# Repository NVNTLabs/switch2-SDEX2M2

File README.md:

# NVNT's SDEX2M2 (MicroSD Express to M.2) Adapter Project

SDEX2M2 (Micro**SD** **Ex**press to **M2**) is an adapter for the Nintendo Switch 2 which converts the MicroSD Express slot to a NVME M.2 (M-Key) slot. Think MicroSD Express cards are difficult to find or expensive? Looking to expand your storage for cheaper? Just use the NVME M.2 SSD that you have, and/or can easily find! The project is open source hardware under the GPLv3 License.

This project also encompasses the sister-project of "MicroSD Express to SD Express" adapter, which is a pin-to-pin conversion kit allowing full size SD Express cards to be used on the Nintendo Switch 2.

---

## 📚 Table of Contents
- **Introduction**
  - [Goals](#goals)
  - [Status](#status)
  - [Warnings](#warnings)
- **Assets & Hardware Info**
  - [Bill of Materials (BOM)](#bill-of-materials-bom)
  - [PINOUT & LEGEND](#pinout--legend)
    - [MicroSD Express to M.2 NVMe Mapping](#microsd-express-to-m2-nvme-mapping)
    - [M.2 NVMe Pinout](#m2-nvme-pinout)
    - [MicroSD Express Pinout](#microsd-express-pinout)
- **PCB's / Boards**
  - [Wiring Schematic](#wiring-schematic)
  - [MicroSD Express Dummy Card](#microsd-express-dummy-card)
  - [MicroSD Express to FPC Flex Cable Connector](#microsd-express-to-fpc-flex-cable-connector)
  - [MicroSD Express Breakout Board](#microsd-express-breakout-board)
  - [NVMe M.2 SSD Breakout Board](#nvme-m2-ssd-breakout-board)
  - [MicroSD Express to SD Express Prototype Adapter](#microsd-express-to-sd-express-prototype-adapter)
  - [SDEX2M2 MicroSD Express to NVMe M.2 Prototype Pin-to-Pin Adapter WIP](#sdex2m2-microsd-express-to-nvme-m2-prototype-pin-to-pin-adapter)
  - [MicroSD Express Sniffer for Switch 2 Handshake (UPDATED!) - USE THIS FOR SIGNAL CAPTURING](#microsd-express-sniffer)
- [License](#license)

---

## How is this possible?

This is possible because the Nintendo Switch 2's MicroSD Express slot supports the SD Express 7.1 standard, which exposes a **true PCIe Gen3 x1 interface** and utilizes the **NVMe protocol** for communication.

This adapter simply maps PCIe x1 from the Switch 2’s MicroSD Express slot to a standard M.2 2230 NVMe SSD. After further research and review from users, an onboard mcu/fpga will be required for the handshake process with the Switch 2.

Currently, we've developed a sniffer board which will be used to facilitate this.

---

## Goals

- ✅ Create Pinout & Pin Definitions (UPDATED!)
- ✅ Create Footprints for MicroSD Express
- ✅ Create Schematic for PCB layout
- ✅ Create Dummy MicroSD Express Card V2
- ✅ Create M.2 Breakout for prototyping (Updated 2-layer PCB)
- ✅ Create MicroSD Express Breakout Board V0.1 (Updated 2-layer PCB)
- ✅ Create MicroSD Express to SD Express Adapter (Experimental, Updated 2-layer PCB)
- ✅ Create BOM for fabrication and sourcing (WIP)
- ✅ Create MicroSD Express to NVMe M.2 SSD Pin to Pin Adapter (Proof of concept)
- ✅ Create basic 3D printable enclosures/shells for the PCBs
- ✅ Create MicroSD Express Sniffer PCB for capturing Nintendo Switch 2 Handshake (for getting NVMe drives to be functional!)
- ✅ Update MicroSD Express Sniffer PCB with new components and better grounding
- 🔲 Create MicroSD Express to NVMe M.2 SSD Adapter with FPGA/MCU Proto (for handshake with Nintendo Switch 2) **(in progress)**
- ✅ Create MicroSD Express to Flex Cable Adapter
- 🔲 Create Flex Cable to NVMe Adapter **(in progress)**
- 🔲 Create MicroSD Express to NVMe M.2 SSD Dock **(in progress)**

---

## Status

Work in progress. Currently, a prototype with handshake capability with the Switch 2 and also designs for the final product design are being worked on.

An early proof of concept prototype of the SDEX2M2 MicroSD Express to NVMe M.2 SSD Adapter has been made, but it does lack Switch 2 compatibility. 

**For prototyping, a new MicroSD Express sniffer has been uploaded which is used for capturing the signal/handshake that the Nintendo Switch 2 uses for communicating with the MicroSD Express card. With this, we are one step closer to our goal!**

Additionally, production-ready 2-layer PCBs for the MicroSD Express breakout board, NVMe breakout board, and the MicroSD Express to FPC Connector (which may be used in the final design) have been uploaded.

The MicroSD Express to SD Express adapter production ready prototype board has been uploaded as well, for users with full-size SD Express cards.

Basic 3D printable shells have been added too, for convenience.

---

## Warnings

- Use at your own risk. We are **not liable** for any damage to your drive, Switch 2, or other devices.
- Only use **low-voltage, low-power M.2 2230 NVMe drives**.
- **Do not use this in legacy MicroSD slots** (e.g., original Nintendo Switch).
  
---

## Bill of Materials (BOM)

| Reference | Quantity | Description                             | Part Number        | Manufacturer   |
|-----------|----------|-----------------------------------------|--------------------|----------------|
| J2        | 1        | M.2 Socket (M-Key, 2230)                | 114020             | Amphenol       |
| FB1       | 1        | Ferrite Bead 220Ω@100MHz 0603           | BLM18PG221SN1D     | Murata/OEM     |
| PCB       | 1        | 4-Layer PCB        | N/A                | Fabricated         | *              |
|*          | 1        | 10kΩ – 100kΩ Pull Up Resistor (Optional) | N/A               | *              |

The optional resistor is for the PERST# lane, may help with state when idle. Not sure if needed until prototyping commences.

---

## PINOUT & LEGEND

### MicroSD Express to M.2 NVMe Mapping

| microSD Express Pin  | PCIe Function | M.2 M-Key Pin(s) | M.2 Function         |
| -------------------- | ------------- | ---------------- | -------------------- |
| 7 (Row 1)            | REFCLK+       | B10              | REFCLK+              |
| 8 (Row 1)            | REFCLK−       | B11              | REFCLK−              |
| 2 (Row 1)            | PERST#        | A11              | PERST#               |
| 1 (Row 1)            | CLKREQ#       | B8               | CLKREQ#              |
| 11 (Row 2)           | TX+           | B23              | PCIe TX+             |
| 12 (Row 2)           | TX−           | B24              | PCIe TX−             |
| 14 (Row 2)           | RX-           | A21              | PCIe RX+             |
| 15 (Row 2)           | RX+           | A22              | PCIe RX−             |
| 4 (Row 1)            | 3.3V VDD      | B2, B3, B4       | 3.3V Power           |
| 6, 10, 13, 16     | GND           | A1, A4, etc.     | Ground               |

---

### M.2 NVMe Pinout

| Pin     | Name     | Function                 |
|---------|----------|--------------------------|
| A11     | PERST#   | PCIe Reset               |
| A21     | RX+      | PCIe RX+ (to host)       |
| A22     | RX−      | PCIe RX− (to host)       |
| B10     | REFCLK+  | PCIe Reference Clock +   |
| B11     | REFCLK−  | PCIe Reference Clock −   |
| B23     | TX+      | PCIe TX+ (from host)     |
| B24     | TX−      | PCIe TX− (from host)     |
| B2–B4   | 3.3V     | Power Supply             |
| A1, A4  | GND      | Ground Pins              |

---

### MicroSD Express Pinout

In SD Mode &* PCIe Mode

| Pin | Row 1 Contact | SD Mode Function | PCIe Mode Function               |
| --- | ------------- | -------------------- | ---------------------------- |
| 1   | DAT2          | Data Line 2          | CLKREQ# (Power / Signal Mgmt)         |
| 2   | DAT3 / CD     | Data Line 3 / CD     | PERST# (Reset)               |
| 3   | CMD           | Command Line         | CMD (unused in PCIe mode)    |
| 4   | VDD           | 3.3V Power           | 3.3V Power                   |
| 5   | CLK           | Clock Line           | CLK (unused in PCIe mode)    |
| 6   | VSS           | Ground               | Ground                       |
| 7   | DAT0          | Data Line 0          | REFCLK+ (PCIe Ref Clock)     |
| 8   | DAT1          | Data Line 1          | REFCLK− (PCIe Ref Clock)     |

| Pin | Row 2 Contact   | PCIe Function                 |
| --- | --------------- | ----------------------------- |
| 9   | 1V8             | 1.8 Volts                     |
| 10  | VSS2            | Ground for isolation          |
| 11  | TX+             | PCIe TX+ (Transmit)           |
| 12  | TX-             | PCIe TX- (Transmit)           |
| 13  | VSS3            | Ground for isolation          |
| 14  | RX-             | PCIe RX- (Receive)            |
| 15  | RX+             | PCIe RX+ (Receive)            |
| 16  | VSS4            | Ground for isolation          |
| 17  | 1V2             | 1.2 Volts                     |

Please note: Row 2 is only operational in PCIe Mode. Row 2 is based on M1cha's (https://github.com/M1cha/sdexpress_pcbs) schematic.

---

### MicroSD Express Card to SD Express Slot Pinout

| **MicroSD Express Pin** | **Function (PCIe Mode)**  | **SD Express Slot Pin** | **Function in Slot** | 
| ----------------------- | ------------------------- | ----------------------- | -------------------- | 
| 1 DAT2                  | CLKREQ#                   | 51                      | CLKREQ# (Power / Signal Mgmt) | 
| 2 DAT3 / CD             | PERST#                    | 52                      | PERST# (Reset line)  |
| 3 CMD                   | CMD (unused)              | —                       | CMD (unused in PCIe mode) | 
| 4 VDD                   | 3.3V VDD                  | 18, 48                  | VDD                  |
| 5 CLK                   | CLK (unused)              | —                       | —                    | 
| 6 VSS                   | GND (VSS1)                | 17, 47, 49, 50          | GND                  |
| 7 DAT0                  | REFCLK+                   | 45                      | REFCLK+              | 
| 8 DAT1                  | REFCLK−                   | 46                      | REFCLK−              | 
| 9 1V8                   | 1.8V VDD (VDD2)           | 1, 2, 3 (often shared)  | VDD 1.8 Volts        | 
| 10 VSS2                 | GND (VSS2)                | 17, 47, etc.            | GND (GND Ground for isolation)| 
| 11 TX+                  | TX+                       | 39                      | PCIe TX+ (Transmit)  |
| 12 TX-                  | TX−                       | 41                      | PCIe TX- (Transmit)  |
| 13 VSS3                 | GND  (VSS3)               | 17, 47, etc.            | GND (Ground for isolation)| 
| 14 RX-                  | RX−                       | 35                      | PCIe RX- (Receive)|
| 15 RX+                  | RX+                       | 37                      | PCIe RX+ (Receive)|
| 16 VSS4                 | GND (VSS4)                | 17, 47, etc.            | GND (Ground for isolation)|                 
| 17 1V2                  | 1.2V VDD (VDD3, optional) | —                       | Not used (May be unused)|

Note: WIP

---

### Wiring Schematic

Still a WIP. Some discrepencies may exist.

---

### MicroSD Express Dummy Card

A dummy card has been created (thanks to M1cha's design examples!), for reference. Files have been attached.

---

### MicroSD Express to FPC Flex Cable Connector

A MicroSD Express to Flex Cable Connector (FPC) has been created for reference. Schematic, Geberer and PCB files have been attached.

---

### MicroSD Express Breakout Board

A production-ready 2-layer breakout board for MicroSD Express has been created (codenamed: "The Key"). Files have been attached in the repo. The purpose of this is for prototyping with a breadboard.

---

### NVMe M2 SSD Breakout Board

A breakout board for a NVMe M.2 SSD slot (M-key) has been created. Files have been attached in the repo. The purpose of this is for prototyping with a breadboard.

---

### MicroSD Express to SD Express Prototype Adapter

An extremely experimental production ready MicroSD Express to **Full Size** SD Express Slot adapter has been made. The purpose of this is to allow full size SD Express cards to be inserted into the Nintendo Switch 2.

Please be aware that it is untested as of the time of writing.

---

### SDEX2M2 MicroSD Express to NVMe M.2 Prototype Pin-to-Pin Adapter

A production-ready (but experimental) 2-layer PCB for the SDEX2M2 MicroSD Express to NVMe M.2 adapter has been uploaded. 

Please note that this is a pin-to-pin adapter, and is **not capable of completing the handshake with Nintendo Switch 2**. It is a proof of concept board.

---

### MicroSD Express Sniffer

**Newly updated!**

A experimental PCB MicroSD Express sniffer has been uploaded and updated. **This is used for capturing the handshake signal/commands from the Nintendo Switch 2**, which will be used to create the final SDEX2M2 Switch 2 NVME M.2 Drive Adapter.

Now updated to use an Amphenol MicroSD Express Slot and with updated grounding for better signal isolation.

---

## License

This hardware design is licensed under the **CERN Open Hardware License Version 2 – Strongly Reciprocal (CERN-OHL-S v2)**.

The software/firmware design is licensed under the **GNU General Public License v3.0 (GPLv3)**

The documentation and readme is licensed under the **Creative Commons Attribution-ShareAlike 4.0 International (CC-BY-SA 4.0)**.

See [LICENSE](LICENSE.txt), [LICENSE-HARDWARE](LICENSE-HARDWARE.txt) and [LICENSE-DOCUMENTATION](LICENSE-DOCUMENTATION.txt) for more information.

---

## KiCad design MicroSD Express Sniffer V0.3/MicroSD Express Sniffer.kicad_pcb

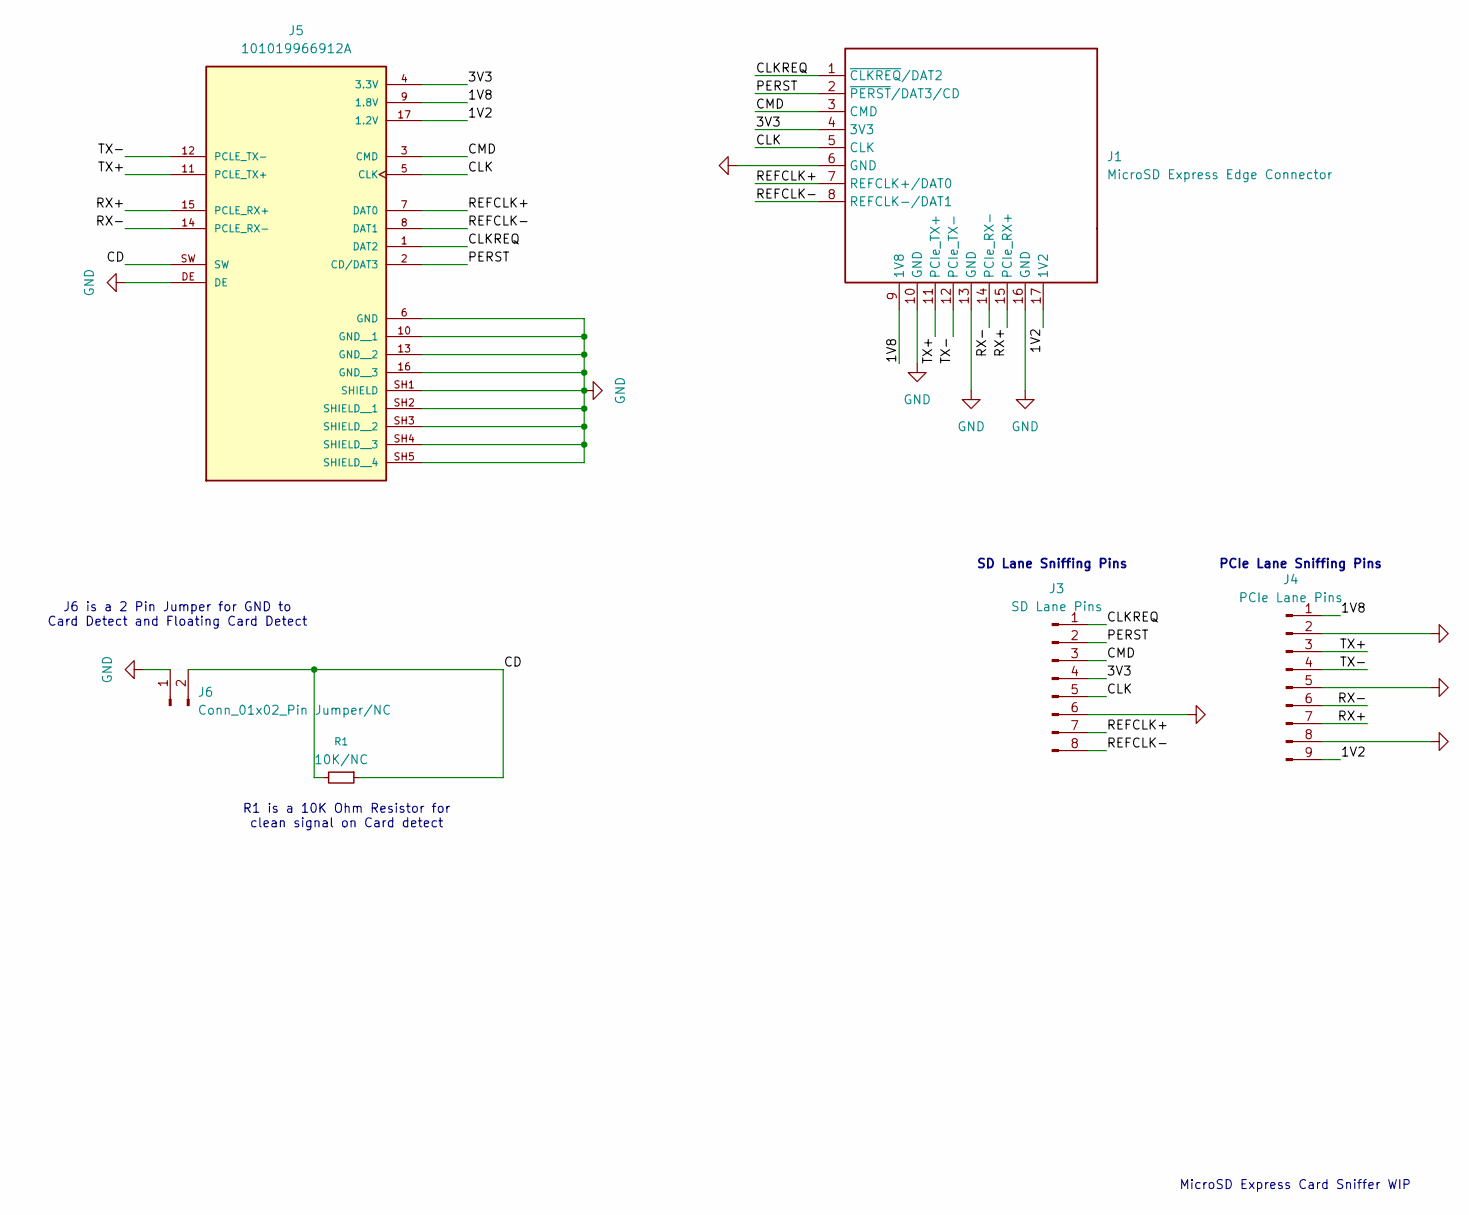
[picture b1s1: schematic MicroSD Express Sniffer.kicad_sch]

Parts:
J1: MicroSD Express Edge Connector; usdex-male-open_bottom
J3: SD Lane Pins; PinHeader_1x08_P2.54mm_Vertical
J4: PCIe Lane Pins; PinHeader_1x09_P2.54mm_Vertical
J5: 101019966912A; AMPHENOL_101019966912A SDEX2M2; PARTREV 10
J6: Conn_01x02_Pin Jumper/NC; PinHeader_1x02_P2.54mm_Vertical
R1: 10K/NC; R_0603_1608Metric

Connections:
/1V2: J1.17 (1V2), J4.9, J5.17 (1.2V)
/1V8: J1.9 (1V8), J4.1, J5.9 (1.8V)
/3V3: J1.4 (3V3), J3.4, J5.4 (3.3V)
/CD: J5.SW, J6.2, R1.1, R1.2
/CLK: J1.5 (CLK), J3.5, J5.5 (CLK)
/CLKREQ: J1.1 (~CLKREQ/DAT2), J3.1, J5.1 (DAT2)
/CMD: J1.3 (CMD), J3.3, J5.3 (CMD)
/PERST: J1.2 (~PERST/DAT3/CD), J3.2, J5.2 (CD/DAT3)
/REFCLK+: J1.7 (REFCLK+/DAT0), J3.7, J5.7 (DAT0)
/REFCLK-: J1.8 (REFCLK-/DAT1), J3.8, J5.8 (DAT1)
/RX+: J1.15 (PCIe_RX+), J4.7, J5.15 (PCLE_RX+)
/RX-: J1.14 (PCIe_RX-), J4.6, J5.14 (PCLE_RX-)
/TX+: J1.11 (PCIe_TX+), J4.3, J5.11 (PCLE_TX+)
/TX-: J1.12 (PCIe_TX-), J4.4, J5.12 (PCLE_TX-)
GND: J1.6 (GND), J1.10 (GND), J1.13 (GND), J1.16 (GND), J3.6, J4.2, J4.5, J4.8, J5.6 (GND), J5.10 (GND__1), J5.13 (GND__2), J5.16 (GND__3), J5.DE, J5.SH1 (SHIELD), J5.SH2 (SHIELD__1), J5.SH3 (SHIELD__2), J5.SH4 (SHIELD__3), J5.SH5 (SHIELD__4), J6.1

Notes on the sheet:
SD Lane Sniffing Pins
R1 is a 10K Ohm Resistor for clean signal on Card detect
J6 is a 2 Pin Jumper for GND to Card Detect and Floating Card Detect
PCIe Lane Sniffing Pins
MicroSD Express Card Sniffer WIP

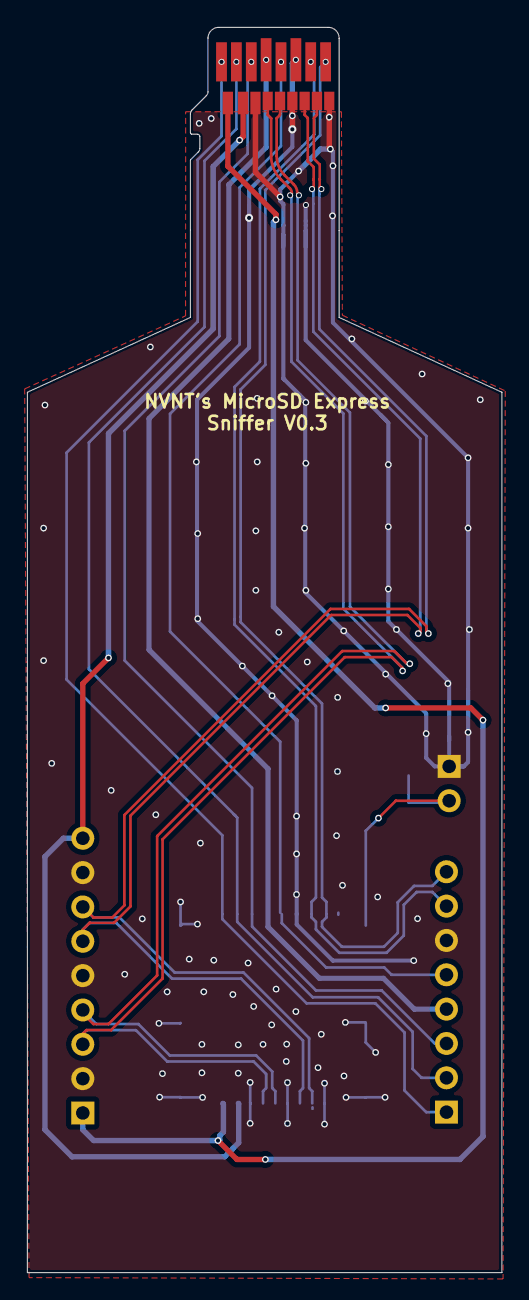
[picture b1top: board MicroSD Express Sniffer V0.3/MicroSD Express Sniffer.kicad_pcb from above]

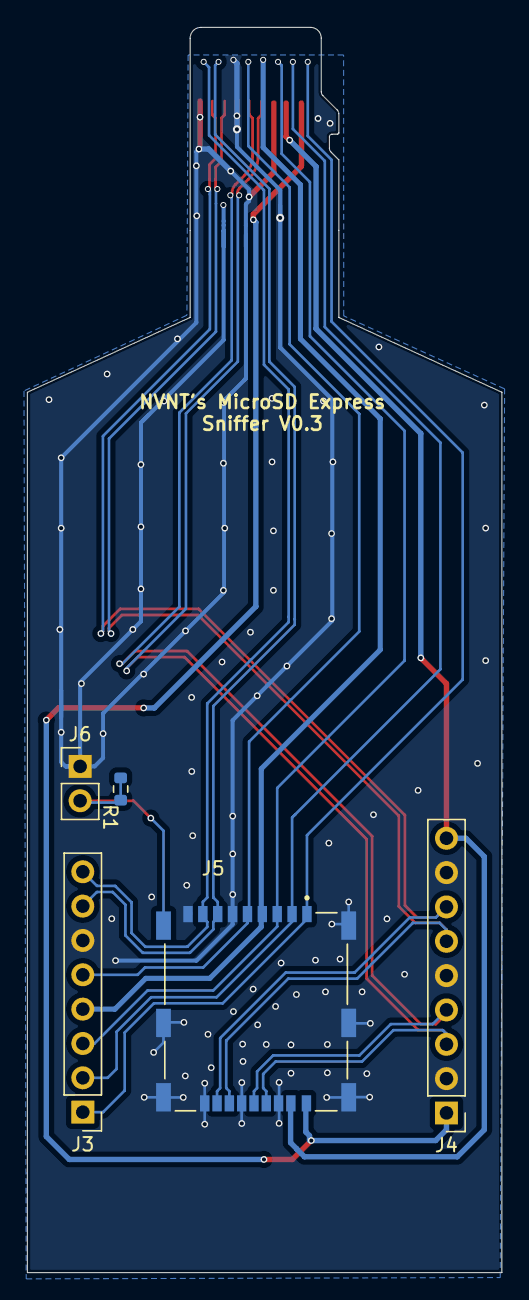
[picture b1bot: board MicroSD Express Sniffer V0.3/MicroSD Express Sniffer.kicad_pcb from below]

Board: 2 copper layers, 35.1 x 92.1 mm, 6 parts (5 on the bottom side), 15 nets.

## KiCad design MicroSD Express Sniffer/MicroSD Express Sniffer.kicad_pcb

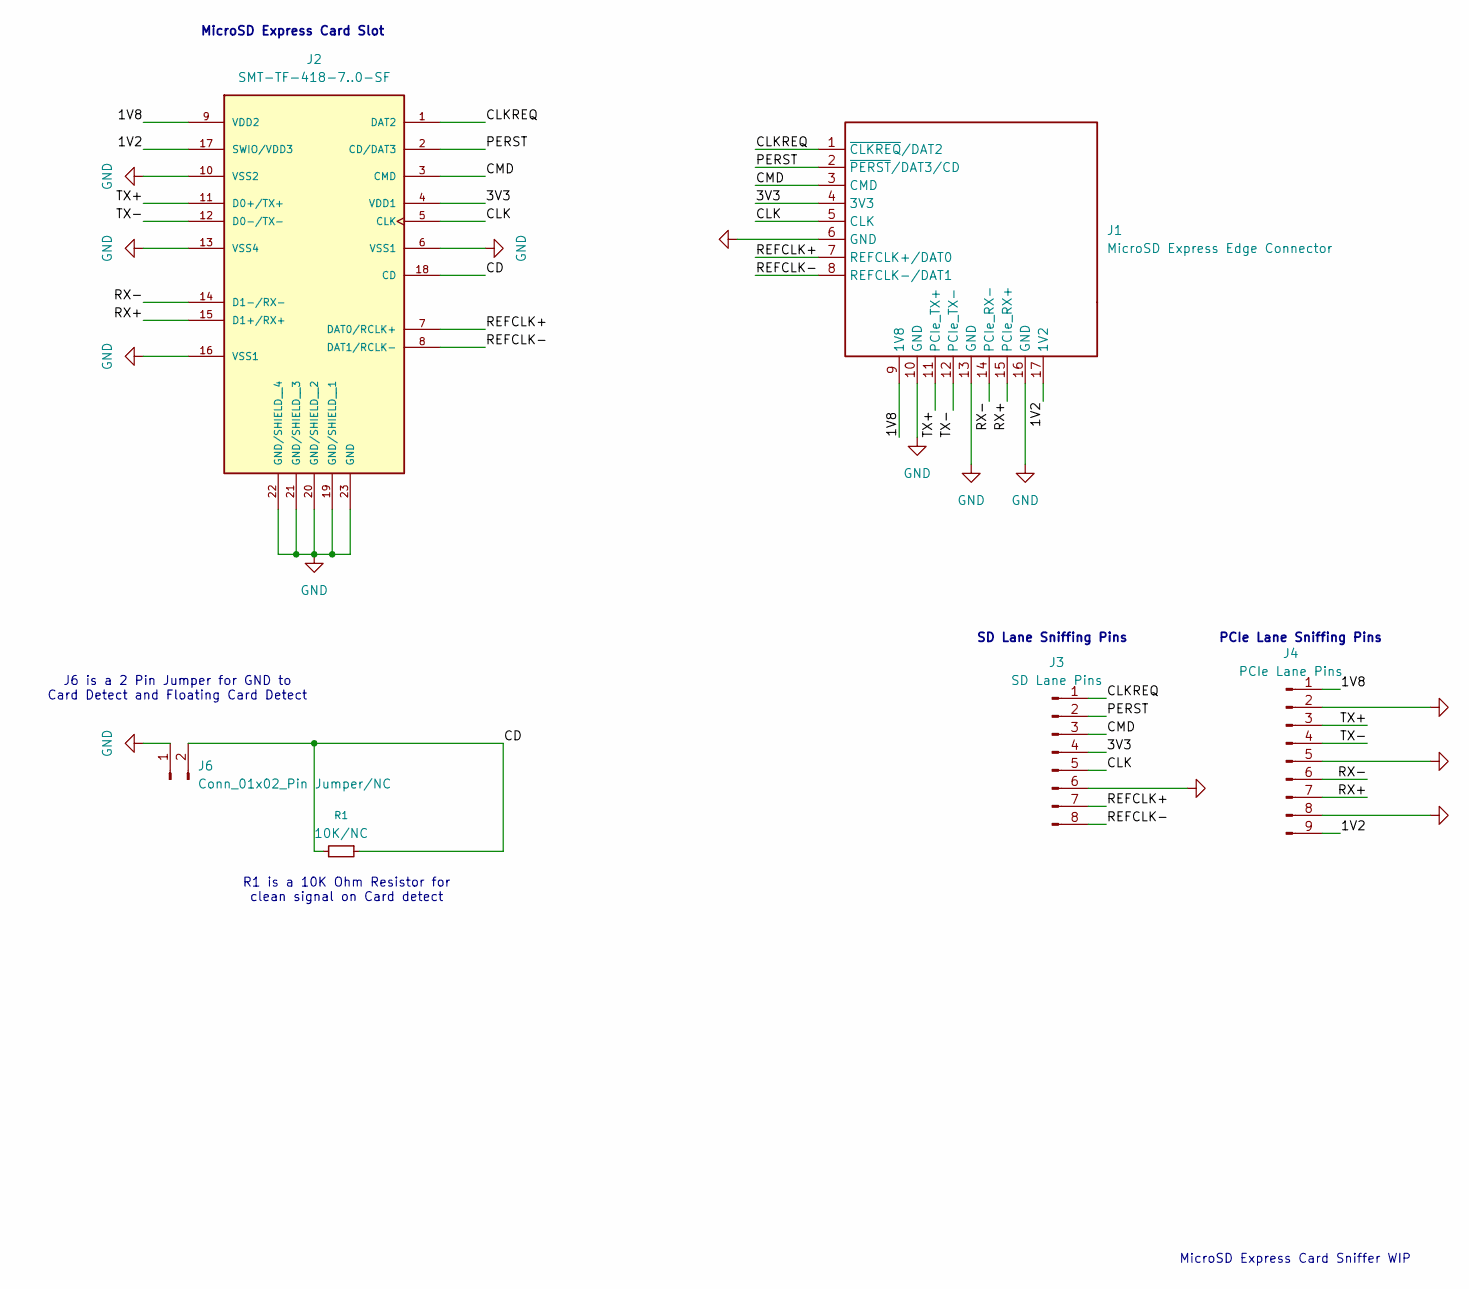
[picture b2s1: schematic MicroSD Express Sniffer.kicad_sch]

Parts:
J1: MicroSD Express Edge Connector; usdex-male-open_bottom
J2: SMT-TF-418-7..0-SF; SMT_TF_418__7.0_SF; PARTREV AX6
J3: SD Lane Pins; PinHeader_1x08_P2.54mm_Vertical
J4: PCIe Lane Pins; PinHeader_1x09_P2.54mm_Vertical
J6: Conn_01x02_Pin Jumper/NC; PinHeader_1x02_P2.54mm_Vertical
R1: 10K/NC; R_0603_1608Metric

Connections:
/1V2: J1.17 (1V2), J2.17 (SWIO/VDD3), J4.9
/1V8: J1.9 (1V8), J2.9 (VDD2), J4.1
/3V3: J1.4 (3V3), J2.4 (VDD1), J3.4
/CD: J2.18 (CD), J6.2, R1.1, R1.2
/CLK: J1.5 (CLK), J2.5 (CLK), J3.5
/CLKREQ: J1.1 (~CLKREQ/DAT2), J2.1 (DAT2), J3.1
/CMD: J1.3 (CMD), J2.3 (CMD), J3.3
/PERST: J1.2 (~PERST/DAT3/CD), J2.2 (CD/DAT3), J3.2
/REFCLK+: J1.7 (REFCLK+/DAT0), J2.7 (DAT0/RCLK+), J3.7
/REFCLK-: J1.8 (REFCLK-/DAT1), J2.8 (DAT1/RCLK-), J3.8
/RX+: J1.15 (PCIe_RX+), J2.15 (D1+/RX+), J4.7
/RX-: J1.14 (PCIe_RX-), J2.14 (D1-/RX-), J4.6
/TX+: J1.11 (PCIe_TX+), J2.11 (D0+/TX+), J4.3
/TX-: J1.12 (PCIe_TX-), J2.12 (D0-/TX-), J4.4
GND: J1.6 (GND), J1.10 (GND), J1.13 (GND), J1.16 (GND), J2.6 (VSS1), J2.10 (VSS2), J2.13 (VSS4), J2.16 (VSS1), J2.19 (GND/SHIELD__1), J2.20 (GND/SHIELD__2), J2.21 (GND/SHIELD__3), J2.22 (GND/SHIELD__4), J2.23 (GND), J3.6, J4.2, J4.5, J4.8, J6.1

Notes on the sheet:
SD Lane Sniffing Pins
R1 is a 10K Ohm Resistor for clean signal on Card detect
J6 is a 2 Pin Jumper for GND to Card Detect and Floating Card Detect
MicroSD Express Card Slot
PCIe Lane Sniffing Pins
MicroSD Express Card Sniffer WIP

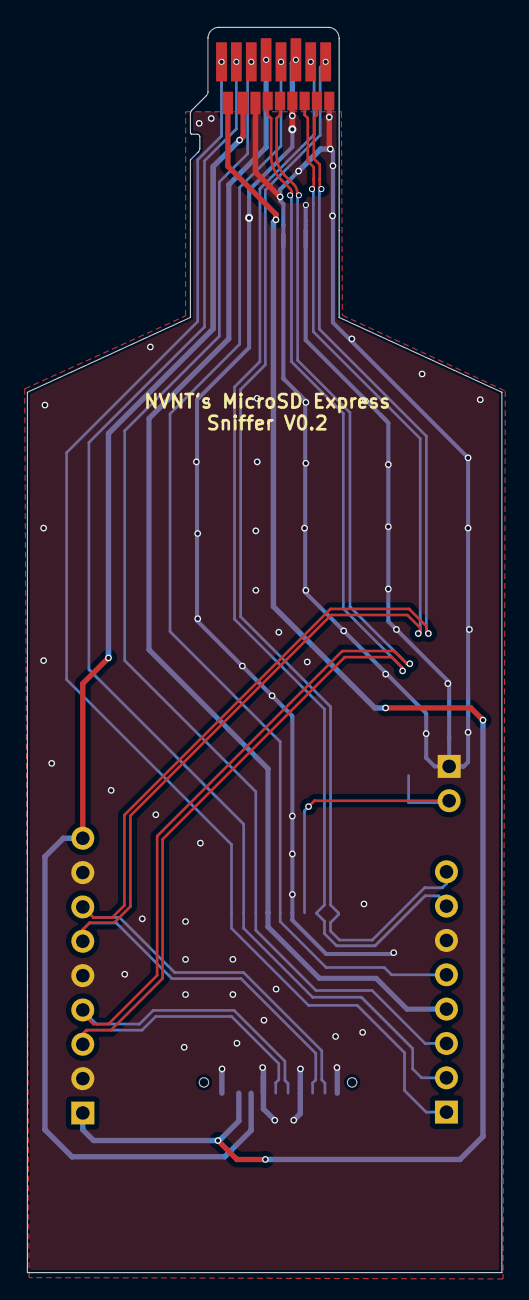
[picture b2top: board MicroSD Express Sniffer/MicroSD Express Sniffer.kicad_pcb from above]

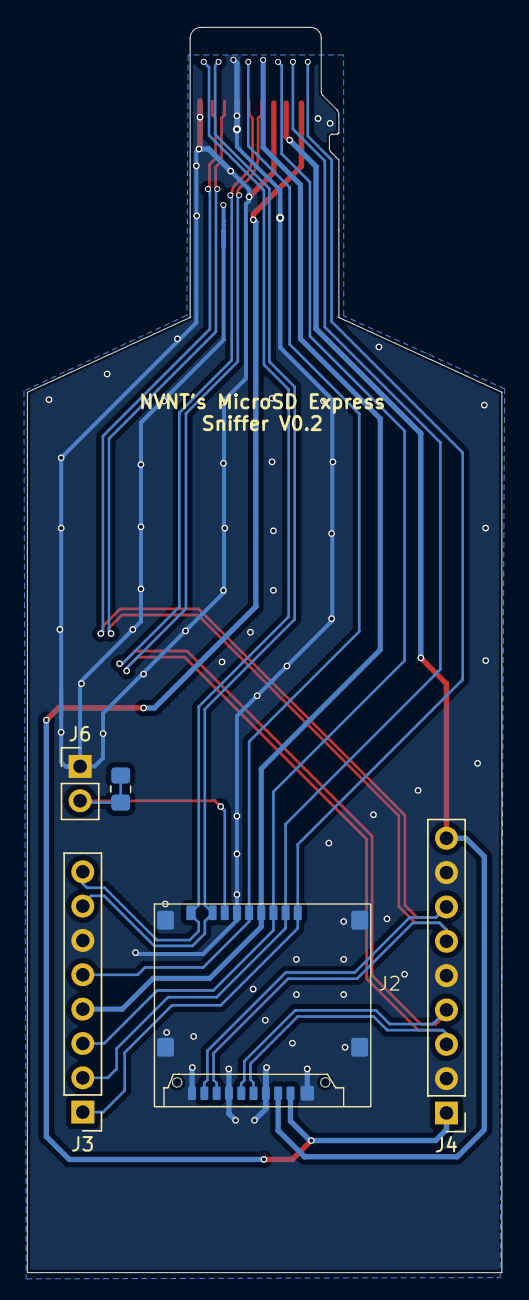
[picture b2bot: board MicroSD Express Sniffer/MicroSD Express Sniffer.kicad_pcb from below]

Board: 2 copper layers, 35.1 x 92.1 mm, 6 parts (5 on the bottom side), 15 nets.

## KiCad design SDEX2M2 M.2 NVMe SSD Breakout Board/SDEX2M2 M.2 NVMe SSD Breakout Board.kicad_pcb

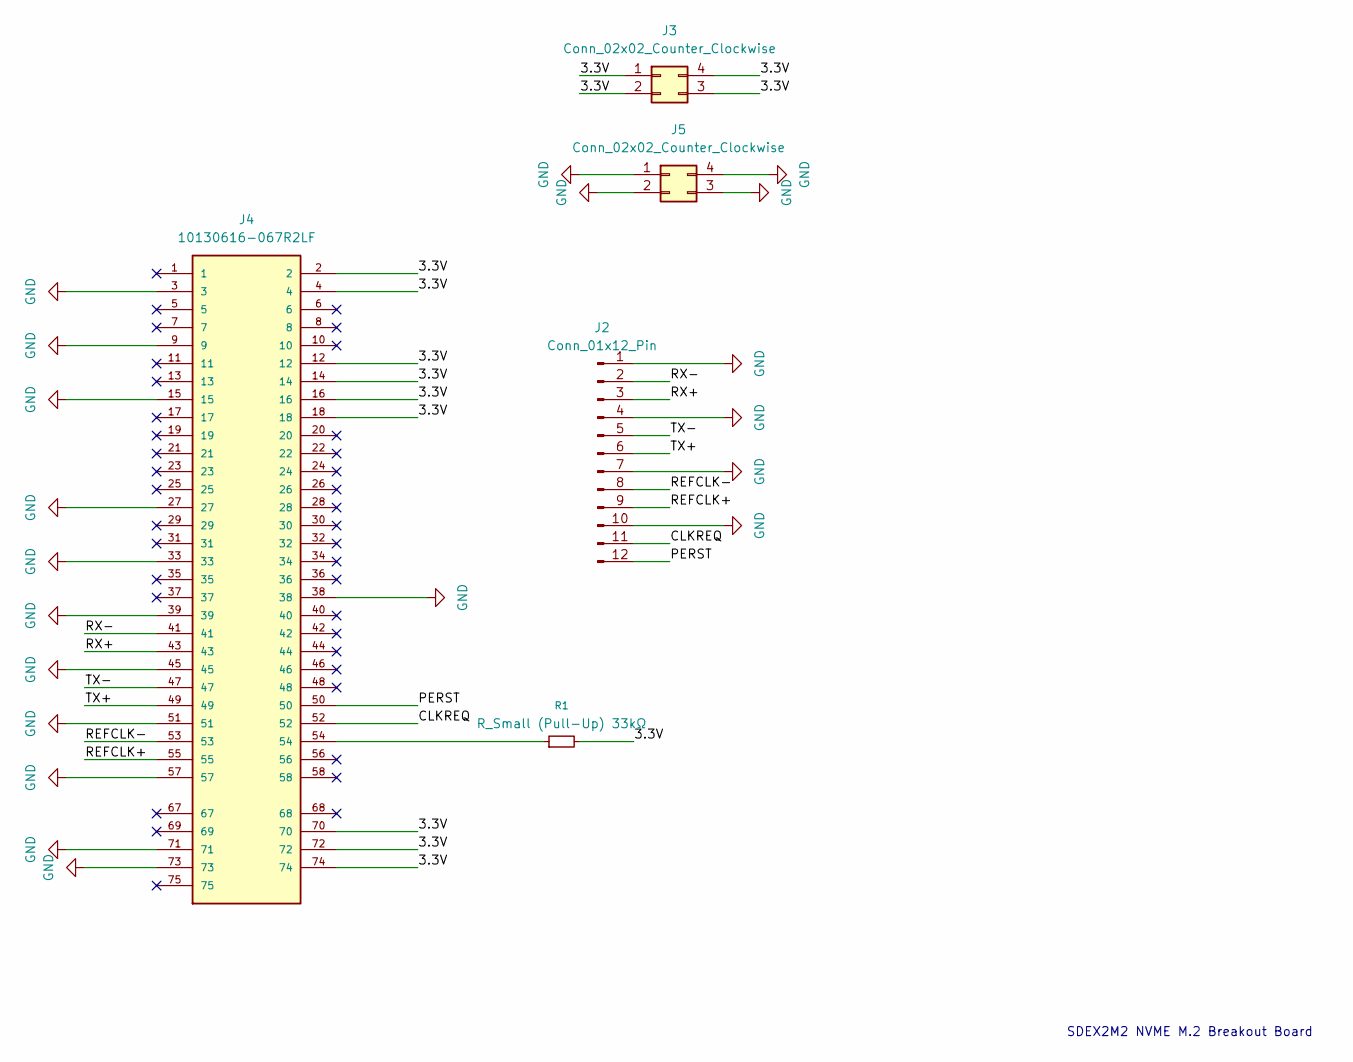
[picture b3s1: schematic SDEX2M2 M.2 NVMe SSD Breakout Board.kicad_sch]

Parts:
J2: Conn_01x12_Pin; PinHeader_1x12_P2.00mm_Vertical
J3, J5: Conn_02x02_Counter_Clockwise; PinHeader_2x02_P2.00mm_Vertical
J4: 10130616-067R2LF; AMPHENOL_10130616-067R2LF; PARTREV C
R1: R_Small (Pull-Up) 33kΩ; R_0603_1608Metric

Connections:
/3.3V: J3.1, J3.2, J3.3, J3.4, J4.2, J4.4, J4.12, J4.14, J4.16, J4.18, J4.70, J4.72, J4.74, R1.2
/CLKREQ: J2.11, J4.52
/PERST: J2.12, J4.50
/REFCLK+: J2.9, J4.55
/REFCLK-: J2.8, J4.53
/RX+: J2.3, J4.43
/RX-: J2.2, J4.41
/TX+: J2.6, J4.49
/TX-: J2.5, J4.47
GND: J2.1, J2.4, J2.7, J2.10, J4.3, J4.9, J4.15, J4.27, J4.33, J4.38, J4.39, J4.45, J4.51, J4.57, J4.71, J4.73, J5.1, J5.2, J5.3, J5.4
unnamed: J4.54, R1.1

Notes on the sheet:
SDEX2M2 NVME M.2 Breakout Board

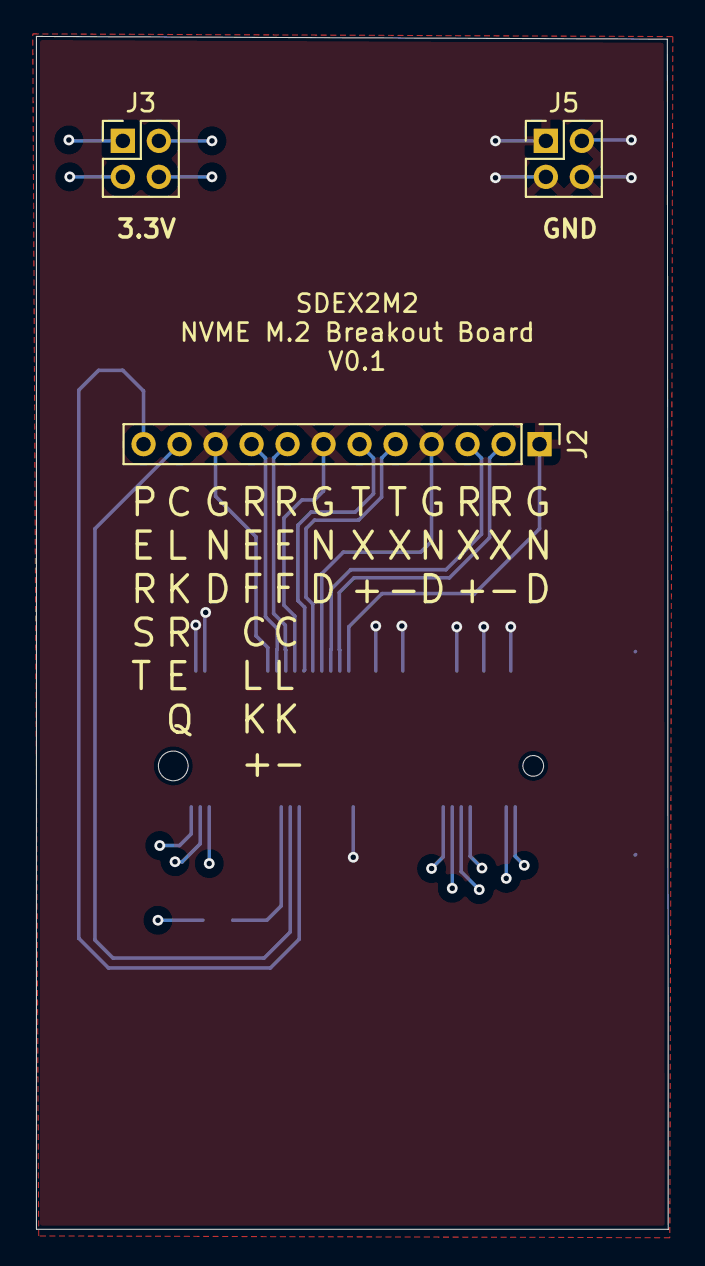
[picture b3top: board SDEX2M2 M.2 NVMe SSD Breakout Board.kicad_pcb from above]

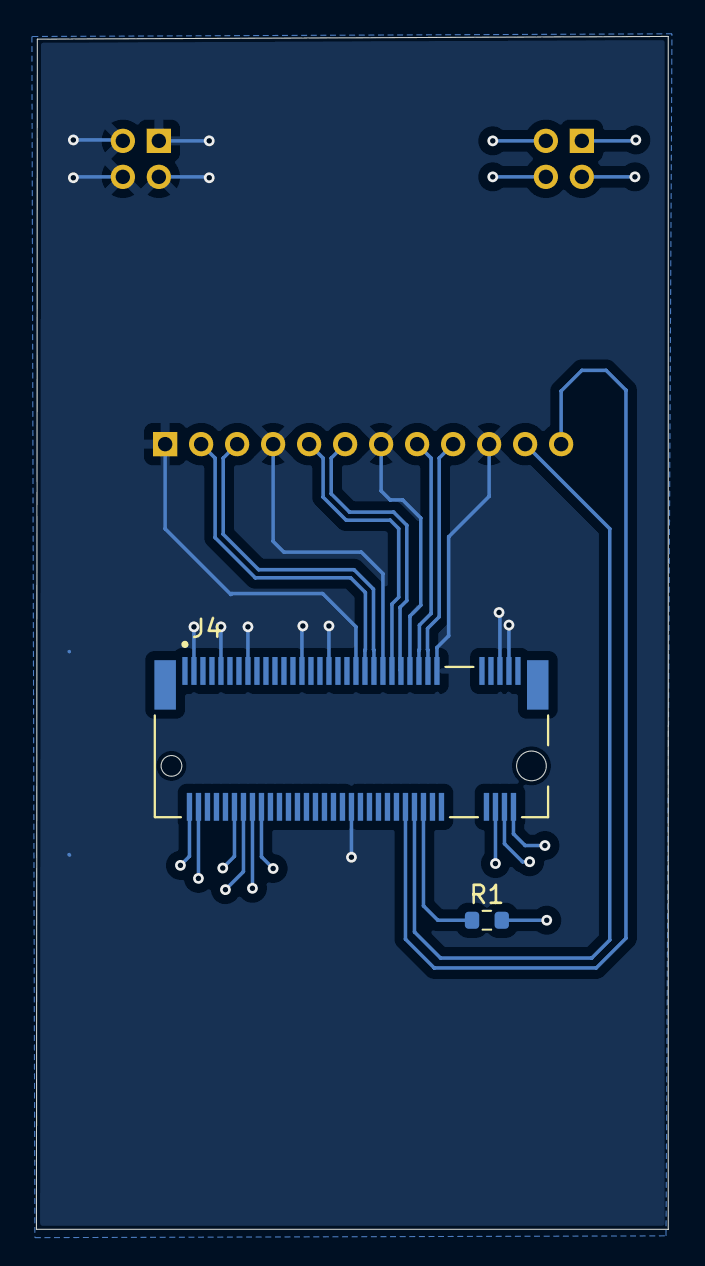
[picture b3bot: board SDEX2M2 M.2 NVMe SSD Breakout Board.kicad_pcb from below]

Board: 6 copper layers, 35.1 x 66.3 mm, 5 parts (2 on the bottom side), 11 nets.

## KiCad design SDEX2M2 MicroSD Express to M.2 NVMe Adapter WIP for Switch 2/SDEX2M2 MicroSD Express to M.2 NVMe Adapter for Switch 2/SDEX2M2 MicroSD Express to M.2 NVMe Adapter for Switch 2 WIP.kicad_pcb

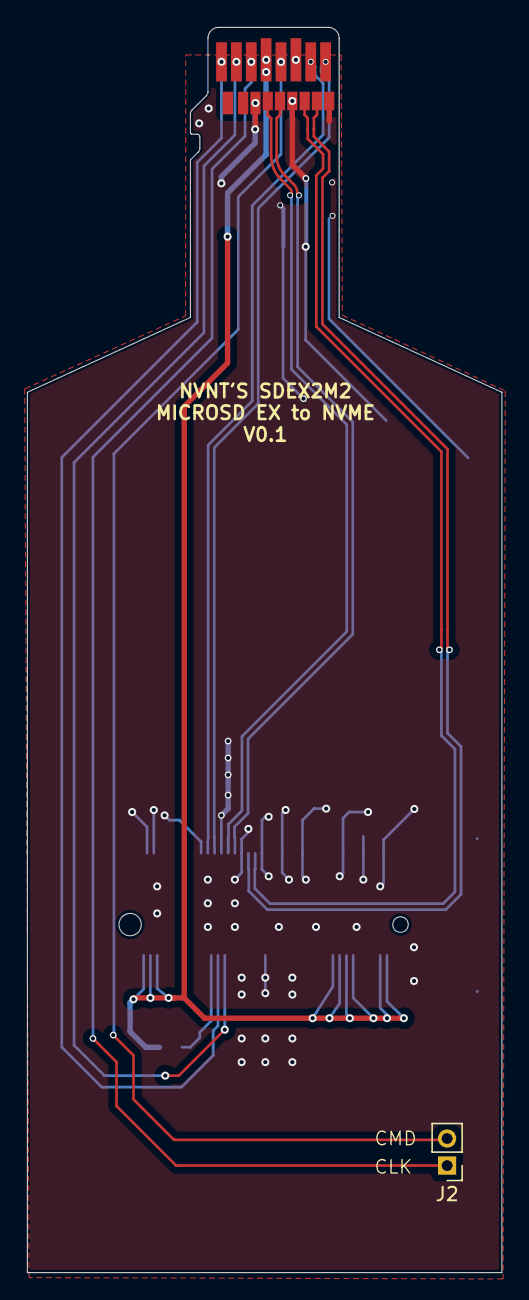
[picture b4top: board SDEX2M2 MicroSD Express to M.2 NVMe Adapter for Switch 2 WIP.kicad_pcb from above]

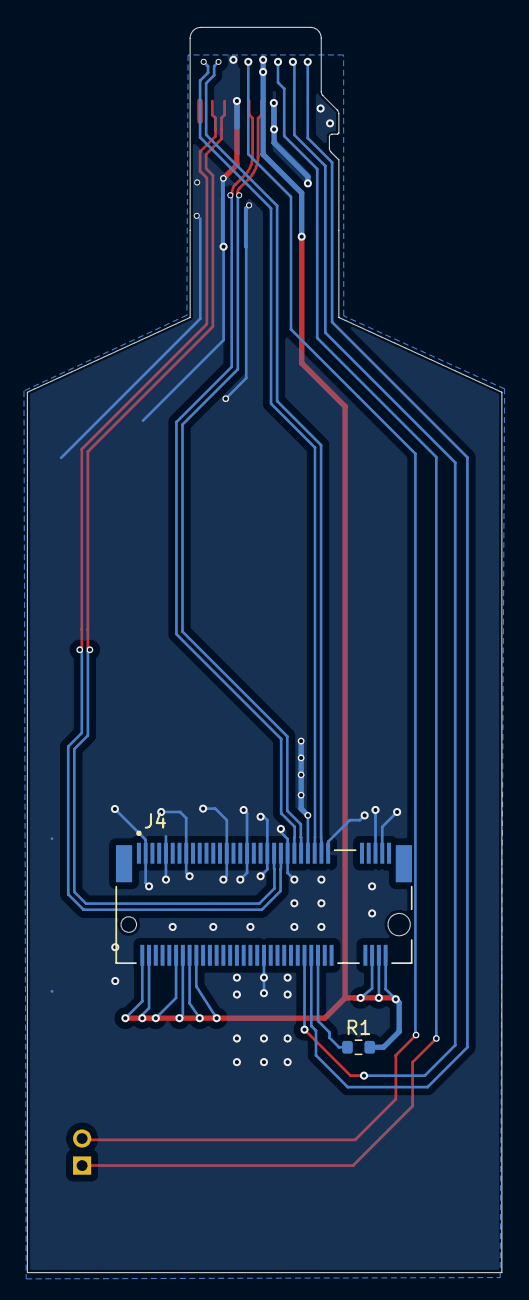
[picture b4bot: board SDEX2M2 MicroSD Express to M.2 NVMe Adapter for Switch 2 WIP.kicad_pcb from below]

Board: 2 copper layers, 35.1 x 92.1 mm, 4 parts (2 on the bottom side), 13 nets.

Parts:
J1: SDEX2M2 MicroSD Express to SD Express Adapter; usdex-male-open_bottom
J2: Conn_01x02_Pin; PinHeader_1x02_P2.00mm_Vertical
J4: 10130616-067R2LF; AMPHENOL_10130616-067R2LF
R1: R_Small (Pull-Up) 33kΩ; R_0603_1608Metric

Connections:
/3.3V: J1.4 (3V3), J4.2, J4.4, J4.12, J4.14, J4.16, J4.18, J4.70, J4.72, J4.74, R1.2
/CLK: J1.5 (CLK), J2.2
/CLKREQ: J1.1 (~CLKREQ/DAT2), J4.52
/CMD: J1.3 (CMD), J2.1
/PERST: J1.2 (~PERST/DAT3/CD), J4.50
/REFCLK+: J1.7 (REFCLK+/DAT0), J4.55
/REFCLK-: J1.8 (REFCLK-/DAT1), J4.53
/RX+: J1.15 (PCIe_RX+), J4.43
/RX-: J1.14 (PCIe_RX-), J4.41
/TX+: J1.11 (PCIe_TX+), J4.49
/TX-: J1.12 (PCIe_TX-), J4.47
GND: J1.6 (GND), J1.10 (GND), J1.13 (GND), J1.16 (GND), J4.3, J4.9, J4.15, J4.27, J4.33, J4.38, J4.39, J4.45, J4.51, J4.57, J4.71, J4.73
unnamed: J4.54, R1.1

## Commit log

2025-06-13 Cleanup & Update Readme
2025-06-16 Added MicroSD Express to SD Express info
2025-06-16 Added MicroSD Express to SD Express Pinout
2025-06-18 Added MicroSD Express Breakout Board info
2025-06-18 Upload MicroSD Express breakout board
2025-06-18 Updated schematic and breakout board
2025-06-19 Added MicroSD Express to SD Express Adapter info
2025-06-19 Added MicroSD Express to SD Express Adapter PCB
2025-06-20 Uploaded M.2 NVMe Breakout Board
2025-06-20 Update README.md
    Updated with NVMe Breakout Board
2025-06-20 Tidying
2025-06-26 Update README.md
    Updated with 2-layer production ready board info & prototype SDEX2M2 adapter info.
2025-06-26 Uploaded 2-layer PCBs + SDEX2M2 Prototype
    Uploaded 2-layer production ready PCBs for each, and uploaded rough SDEX2M2 MicroSD Express to M.2 NVMe prototype.
2025-07-03 Hardware license upload
2025-07-03 Upload documentation license
2025-07-14 Added basic 3D printable shells
2025-07-28 Update LICENSE-HARDWARE.txt
    Tidying
2025-07-29 Update README.md
    Added MicroSD Express to FPC
2025-07-29 Added MicroSD Express to FPC Connector PCB
2025-08-25 Added MicroSD Express sniffer info
    Added info for MicroSD Express Sniffer PCB, required for capturing Switch 2 handshake. One step closer to NVMe!
2025-08-25 Added MicroSD Express Sniffer PCB
    A experimental PCB MicroSD Express sniffer has been uploaded. This is used for capturing the handshake signal/commands from the Nintendo Switch 2.
2025-10-09 Update README.md
    Updated with V0.3 of Switch 2 MicroSD Express Slot Sniffer. Used for capturing the handshake signal which will be used in the final adapter.
2025-10-09 Uploaded Switch 2 MicroSD Express Sniffer V0.3
    Updated the PCB design of the MicroSD Express sniffer to have better grounding and to use name-brand Amphenol MicroSD Express Slot. This is used for capturing the handshake which the final Switch 2 M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
2025-10-20 Update README.md
    Added more info for clarity of Pin-to-pin adapter
